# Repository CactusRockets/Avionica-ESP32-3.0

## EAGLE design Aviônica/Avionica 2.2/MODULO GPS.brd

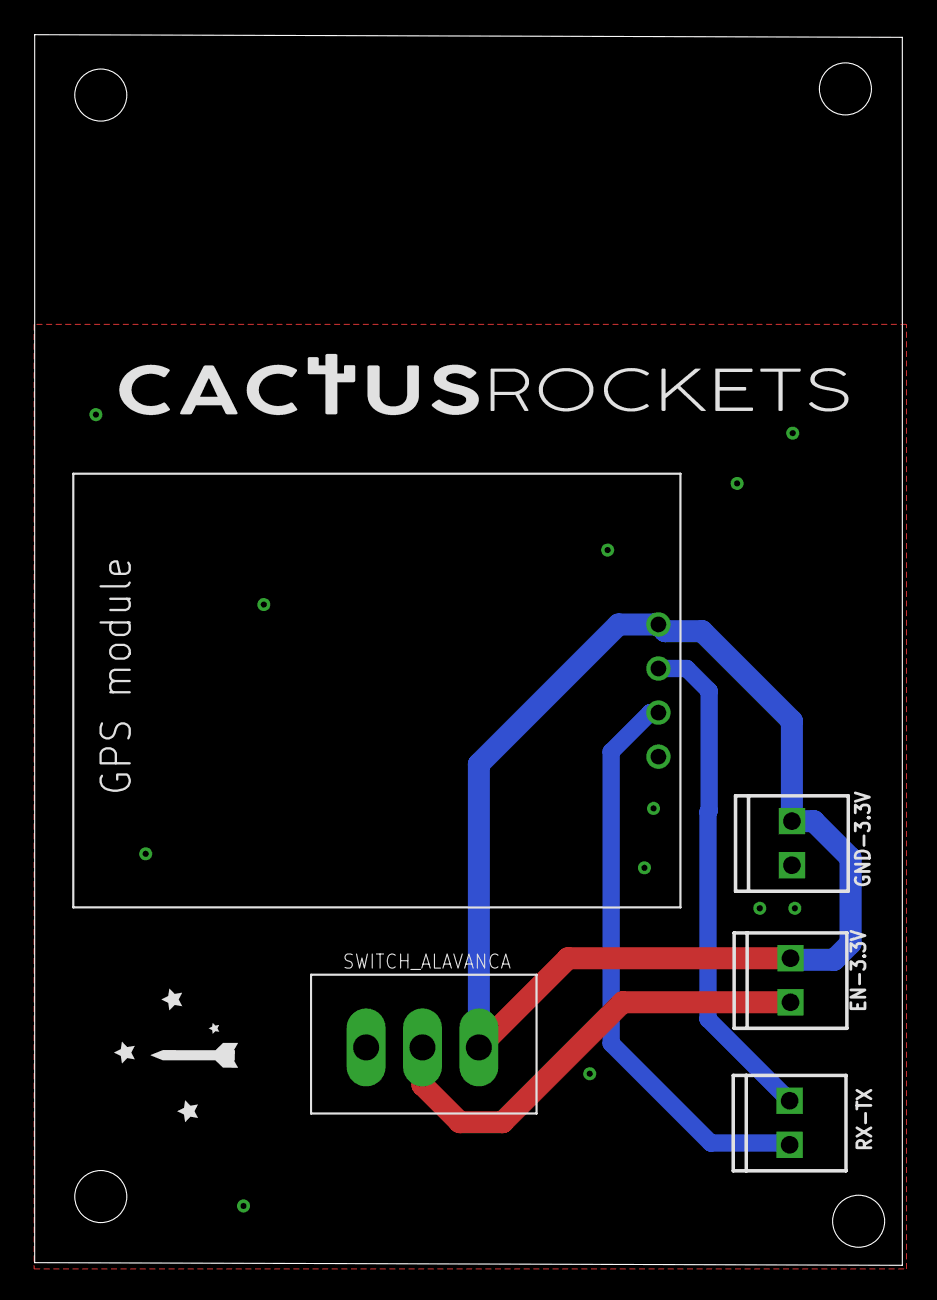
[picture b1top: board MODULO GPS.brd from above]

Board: 2 copper layers, 50.0 x 70.9 mm, 5 parts (0 on the bottom side), 5 nets.

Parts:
EN-3.3V: 1X02_2.54_SCREWTERM
GND-3.3V: 1X02_2.54_SCREWTERM
RX-TX: 1X02_2.54_SCREWTERM
U$1: SWITCH_ALAVANCA; SWITCH_ALAVANCA_FOOTPRINT
U$3: GPS_MODULE; GPS_MODULE_FOOTPRINT

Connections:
ENABLE_SIGNAL: EN-3.3V.P2, U$1.PIN2
GND: GND-3.3V.P2, U$1.PIN1, U$3.GND
RX1_ESP: RX-TX.P2, U$3.TX
TX1_ESP: RX-TX.P1, U$3.RX
V_3V3: EN-3.3V.P1, GND-3.3V.P1, U$1.PIN3, U$3.VCC

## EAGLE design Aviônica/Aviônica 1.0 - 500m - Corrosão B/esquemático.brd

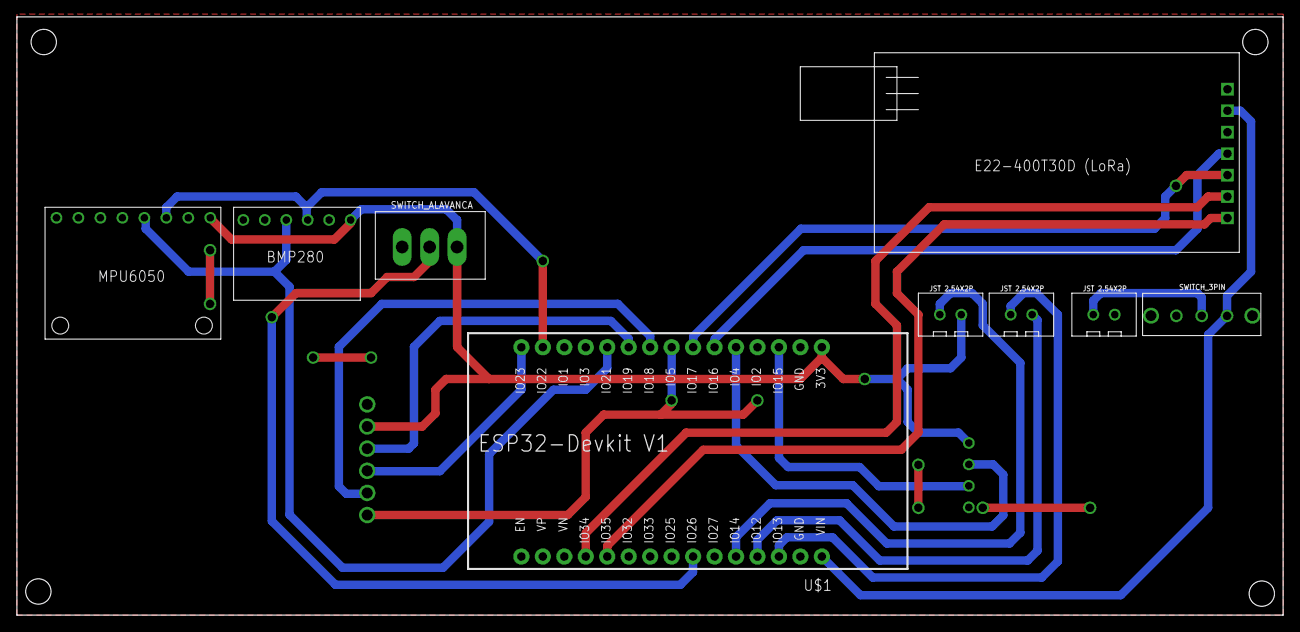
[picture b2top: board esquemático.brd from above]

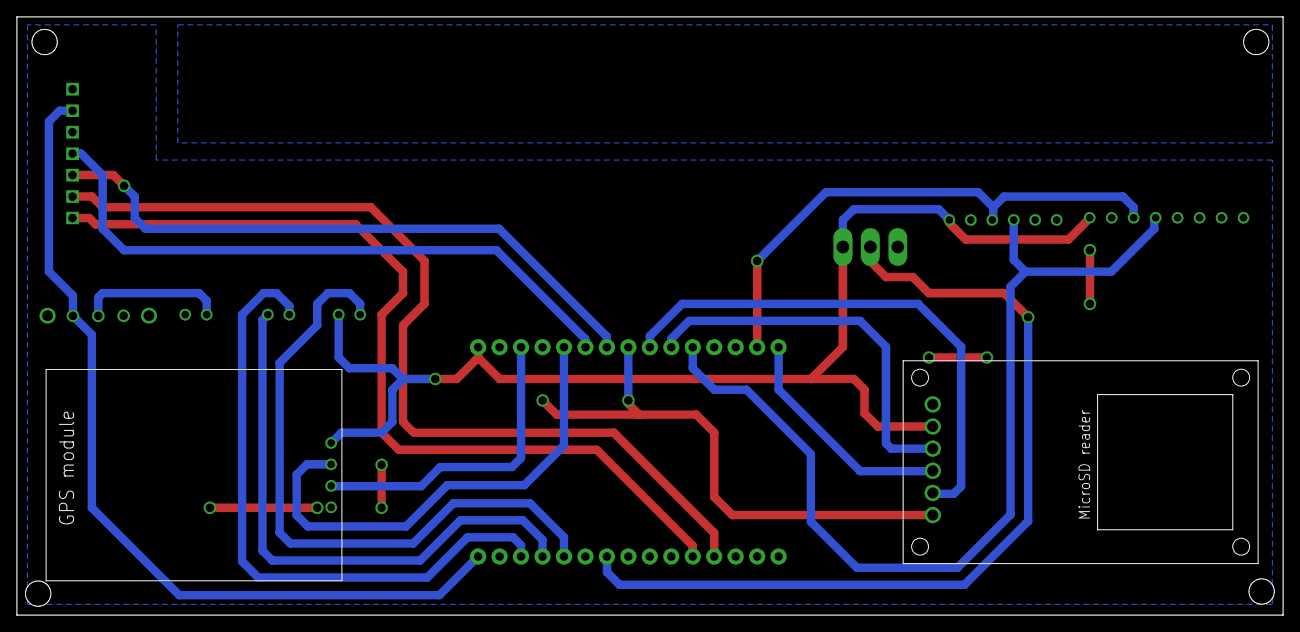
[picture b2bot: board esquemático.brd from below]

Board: 2 copper layers, 149.8 x 70.8 mm, 11 parts (2 on the bottom side), 20 nets.

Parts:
U$1: ESP32DEVKITV1; ESP32-DEVKITV1
U$2: E22-400T30D; E22-400T30D_FOOTPRINT
U$3: GPS_MODULE; GPS_MODULE_FOOTPRINT
U$4: BMP280V1; BMP280_FOOTPRINT
U$5: SWITCH_ALAVANCA; SWITCH_ALAVANCA_FOOTPRINT
U$6: MPU6050V1; MPU6050_FOOTPRINT
U$7: MICROSD_READER; MICROSD_READER_FOOTPRINT
U$8, U$9, U$12: JST2.54X2P; JST2.54X2P_FOOTPRINT
U$11: SWITCH_3PIN

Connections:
BUZZER: U$1.26, U$9.1
CS: U$1.8, U$7.CS
ENABLE_SIGNAL: U$1.24, U$5.PIN2
GND: U$1.2, U$1.29, U$2.GND, U$3.GND, U$4.GND, U$5.PIN1, U$6.GND, U$7.GND, U$12.2
M0: U$1.20, U$2.M0
M1: U$1.19, U$2.M1
MISO: U$1.10, U$7.MISO
MOSI: U$1.15, U$7.MOSI
RX1_ESP: U$1.3, U$3.TX
RX2_ESP: U$1.6, U$2.TXD
SCK: U$1.9, U$7.SCK
SCL: U$1.14, U$4.SCL, U$6.SCL
SDA: U$1.11, U$4.SDA, U$6.SDA
SKIB1: U$1.28, U$8.1
SKIB2: U$1.27, U$8.2
TX1_ESP: U$1.5, U$3.RX
TX2_ESP: U$1.7, U$2.RXD
V_3V3: U$1.1, U$3.VCC, U$4.VCC, U$5.PIN3, U$6.VCC, U$7.VCC, U$9.2
V_BATTERY: U$11.2, U$12.1
V_IN: U$1.30, U$2.VCC, U$11.3

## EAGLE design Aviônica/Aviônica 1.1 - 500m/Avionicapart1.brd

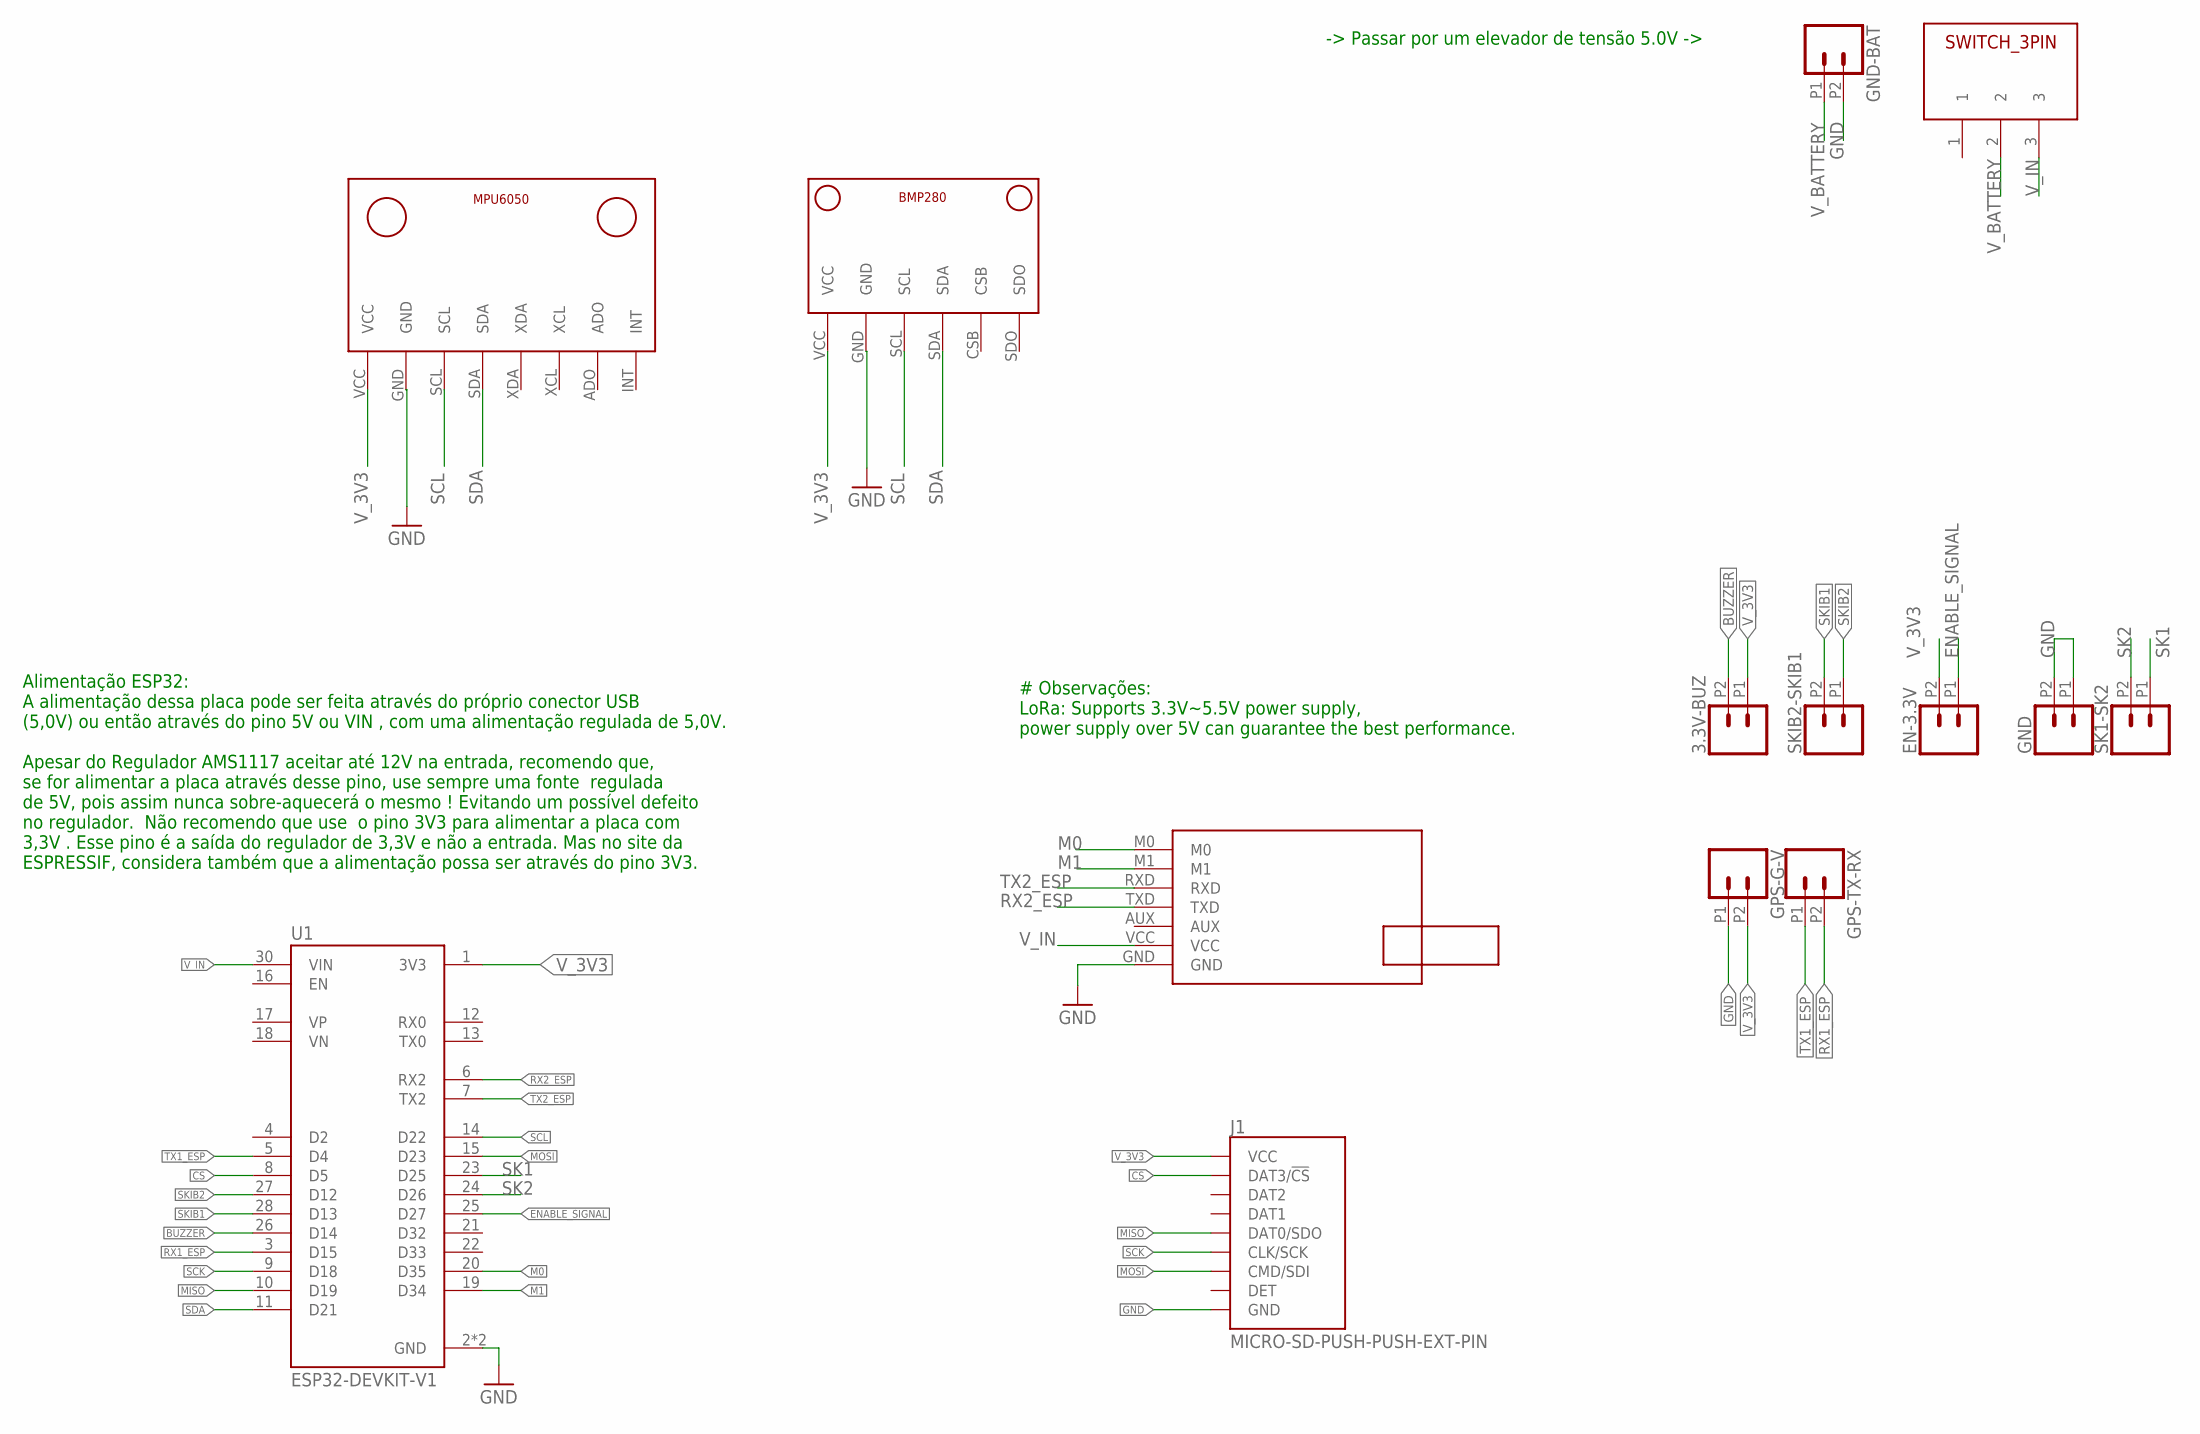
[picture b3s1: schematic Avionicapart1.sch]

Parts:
3.3V-BUZ: CONN_022.54MM_SCREWTERM; 1X02_2.54_SCREWTERM
EN-3.3V: CONN_022.54MM_SCREWTERM; 1X02_2.54_SCREWTERM
GND: CONN_022.54MM_SCREWTERM; 1X02_2.54_SCREWTERM
GND-BAT: CONN_022.54MM_SCREWTERM; 1X02_2.54_SCREWTERM
GPS-G-V: CONN_022.54MM_SCREWTERM; 1X02_2.54_SCREWTERM
GPS-TX-RX: CONN_022.54MM_SCREWTERM; 1X02_2.54_SCREWTERM
J1: MICRO-SD-PUSH-PUSH-EXT-PIN; MICROSD-EXTERNALPIN
SK1-SK2: CONN_022.54MM_SCREWTERM; 1X02_2.54_SCREWTERM
SKIB2-SKIB1: CONN_022.54MM_SCREWTERM; 1X02_2.54_SCREWTERM
U1: ESP32-DEVKIT-V1; MODULE_ESP32_DEVKIT_V1
U$2: E22-400T30D; E22-400T30D_FOOTPRINT
U$4: BMP280V1; BMP280_FOOTPRINT
U$6: MPU6050V1; MPU6050_FOOTPRINT
U$11: SWITCH_3PIN

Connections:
BUZZER: 3.3V-BUZ.P2 (2), U1.26 (D14)
CS: J1.2 (DAT3/!CS!), U1.8 (D5)
ENABLE_SIGNAL: EN-3.3V.P1 (1), U1.25 (D27)
GND: GND.P1 (1), GND.P2 (2), GND-BAT.P2 (2), GPS-G-V.P1 (1), J1.6 (GND), J1.10 (GND), J1.11 (GND), J1.12 (GND), J1.13 (GND), U1.2 (GND), U1.29 (GND), U$2.GND, U$4.GND, U$6.GND
M0: U1.20 (D35), U$2.M0
M1: U1.19 (D34), U$2.M1
MISO: J1.7 (DAT0/SDO), U1.10 (D19)
MOSI: J1.3 (CMD/SDI), U1.15 (D23)
RX1_ESP: GPS-TX-RX.P2 (2), U1.3 (D15)
RX2_ESP: U1.6 (RX2), U$2.TXD
SCK: J1.5 (CLK/SCK), U1.9 (D18)
SCL: U1.14 (D22), U$4.SCL, U$6.SCL
SDA: U1.11 (D21), U$4.SDA, U$6.SDA
SK1: SK1-SK2.P1 (1), U1.23 (D25)
SK2: SK1-SK2.P2 (2), U1.24 (D26)
SKIB1: SKIB2-SKIB1.P2 (2), U1.28 (D13)
SKIB2: SKIB2-SKIB1.P1 (1), U1.27 (D12)
TX1_ESP: GPS-TX-RX.P1 (1), U1.5 (D4)
TX2_ESP: U1.7 (TX2), U$2.RXD
V_3V3: 3.3V-BUZ.P1 (1), EN-3.3V.P2 (2), GPS-G-V.P2 (2), J1.4 (VCC), U1.1 (3V3), U$4.VCC, U$6.VCC
V_BATTERY: GND-BAT.P1 (1), U$11.2
V_IN: U1.30 (VIN), U$2.VCC, U$11.3

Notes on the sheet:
-> Passar por um elevador de tensão 5.0V ->
# Observações: LoRa: Supports 3.3V~5.5V power supply, power supply over 5V can guarantee the best performance.
Alimentação ESP32: A alimentação dessa placa pode ser feita através do próprio conector USB (5,0V) ou então através do pino 5V ou VIN , com uma alimentação regulada de 5,0V. Apesar do Regulador AMS1117 aceitar até 12V na entrada, recomendo que, se for alimentar a placa através desse pino, use sempr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

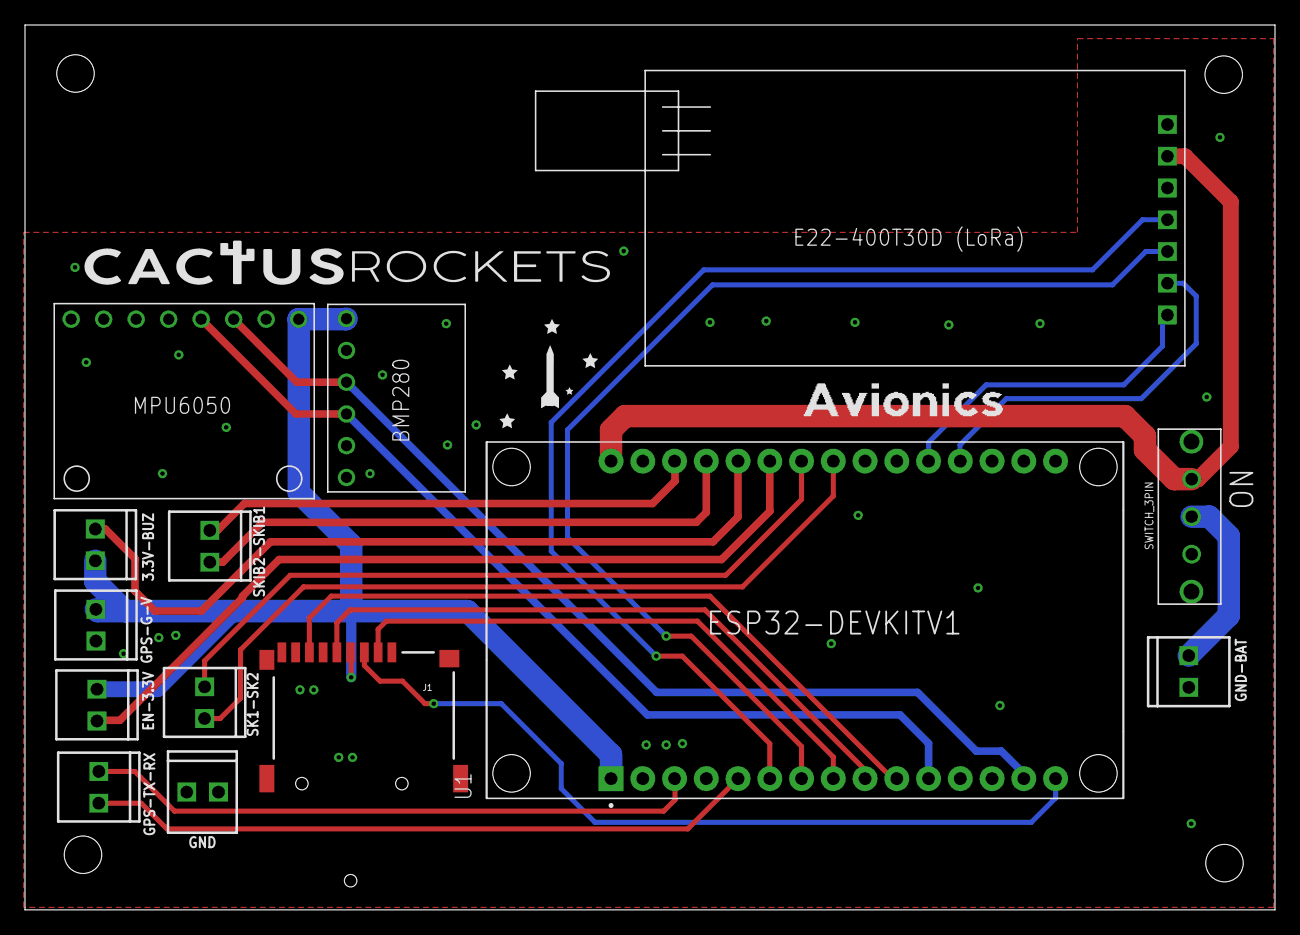
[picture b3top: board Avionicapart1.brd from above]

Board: 2 copper layers, 100.0 x 70.8 mm, 14 parts (0 on the bottom side), 22 nets.

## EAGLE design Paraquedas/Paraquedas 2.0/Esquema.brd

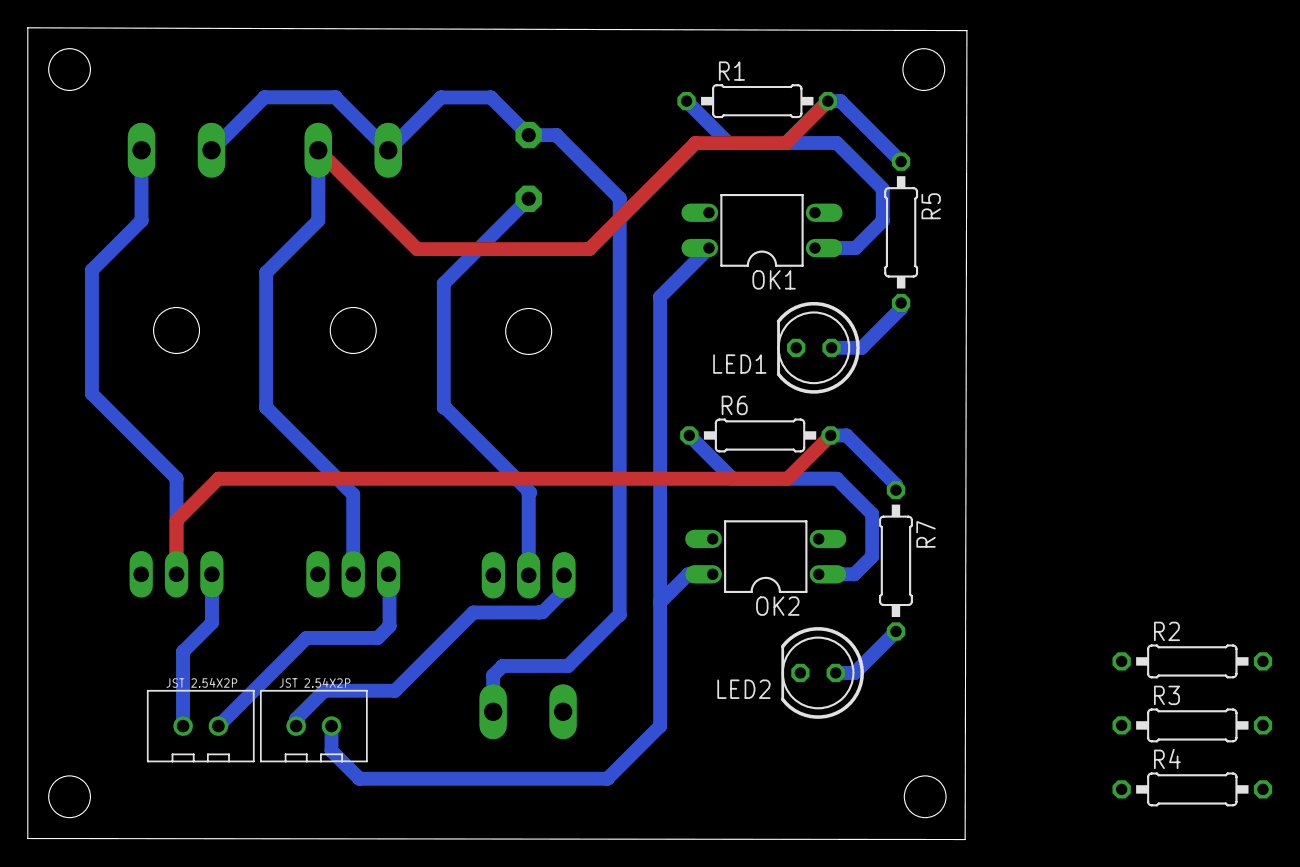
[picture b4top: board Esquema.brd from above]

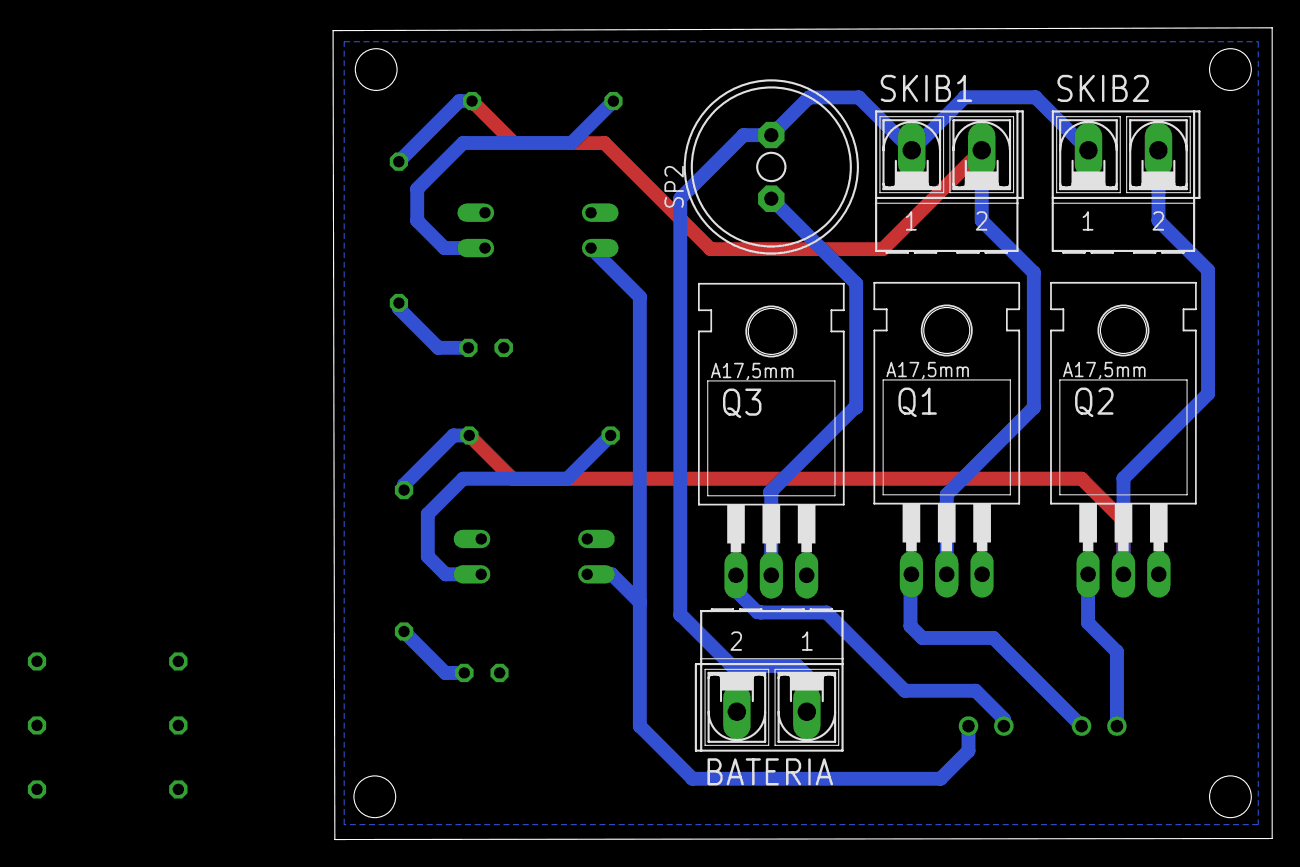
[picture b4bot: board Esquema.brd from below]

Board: 2 copper layers, 67.5 x 58.3 mm, 20 parts (7 on the bottom side), 13 nets.

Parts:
BATERIA: AK500/2-H
LED1, LED2: 5mm; LED5MM
OK1, OK2: PC817; DIL04
Q1, Q2, Q3: IRF540; TO220
R1, R2, R3, R4, R5, R6, R7: 1k; 0207/10
SKIB1, SKIB2: AK500/2-H
SP2: AL11P
U$1, U$2: JST2.54X2P; JST2.54X2P_FOOTPRINT

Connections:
3.3V: OK1.4, OK2.4, U$1.2
BUZZER: Q3.1, U$1.1
GND: BATERIA.2, LED1.K, LED2.K, OK1.2, OK2.2, Q1.3, Q2.3, Q3.3
unnamed: LED2.A, R7.2
unnamed: Q3.2, SP2.-
unnamed: LED1.A, R5.2
unnamed: OK1.1, R1.1
unnamed: OK2.1, R6.1
SKIB1: Q1.1, U$2.2
SKIB1_CONECTOR: Q1.2, R1.2, R5.1, SKIB1.2
SKIB2: Q2.1, U$2.1
SKIB2_CONECTOR: Q2.2, R6.2, R7.1, SKIB2.2
VCC: BATERIA.1, SKIB1.1, SKIB2.1, SP2.+

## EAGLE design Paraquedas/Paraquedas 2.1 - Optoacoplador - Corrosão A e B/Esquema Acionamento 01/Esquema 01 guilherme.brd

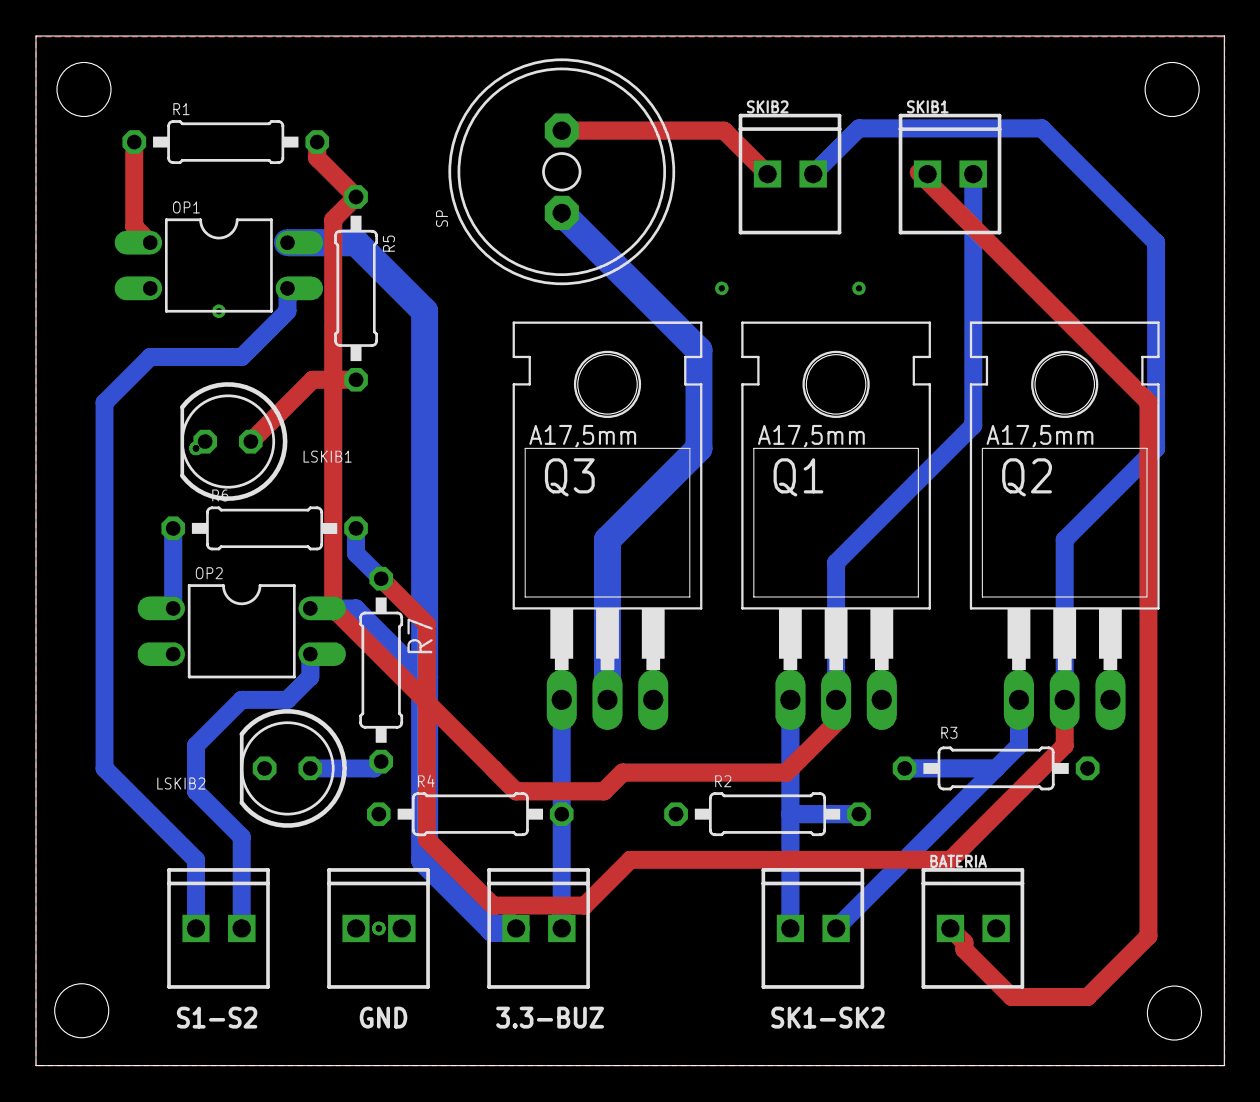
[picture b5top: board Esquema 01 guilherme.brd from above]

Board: 2 copper layers, 66.0 x 57.2 mm, 22 parts (0 on the bottom side), 15 nets.

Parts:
3.3-BUZ: 1X02_2.54_SCREWTERM
BATERIA: 1X02_2.54_SCREWTERM
GND: 1X02_2.54_SCREWTERM
LSKIB1, LSKIB2: 5mm; LED5MM
OP1, OP2: PC817; DIL04
Q1, Q2, Q3: IRF540; TO220
R1, R2, R3, R4, R5, R6, R7: 1k; 0207/10
S1-S2: 1X02_2.54_SCREWTERM
SK1-SK2: 1X02_2.54_SCREWTERM
SKIB1, SKIB2: 1X02_2.54_SCREWTERM
SP: AL11P

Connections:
3.3V: 3.3-BUZ.P2, OP1.4, OP2.4
BUZZER: 3.3-BUZ.P1, Q3.1, R4.2
GND: BATERIA.P1, GND.P1, GND.P2, LSKIB1.K, LSKIB2.K, OP1.2, OP2.2, Q1.3, Q2.3, Q3.3, R2.1, R3.1, R4.1
unnamed: LSKIB2.A, R7.2
unnamed: Q3.2, SP.-
unnamed: LSKIB1.A, R5.2
unnamed: OP1.1, R1.1
unnamed: OP2.1, R6.1
SINAL_SKIB1: OP1.3, S1-S2.P2
SINAL_SKIB2: OP2.3, S1-S2.P1
SKIB1: Q1.1, R2.2, SK1-SK2.P2
SKIB1_CONECTOR: Q1.2, R1.2, R5.1, SKIB1.P1
SKIB2: Q2.1, R3.2, SK1-SK2.P1
SKIB2_CONECTOR: Q2.2, R6.2, R7.1, SKIB2.P1
VCC: BATERIA.P2, SKIB1.P2, SKIB2.P2, SP.+

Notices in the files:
parts and their libraries:
SparkFun-Connectors: Licensing: Creative Commons ShareAlike 4.0 International - https://creativecommons.org/licenses/by-sa/4.0
